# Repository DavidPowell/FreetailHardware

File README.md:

Hardware for Freetail module

Teensy 3.2 Symbol and Footprint adapted from work of Ricardo Band, under MIT License:
https://github.com/XenGi/teensy.pretty
https://github.com/XenGi/teensy_library

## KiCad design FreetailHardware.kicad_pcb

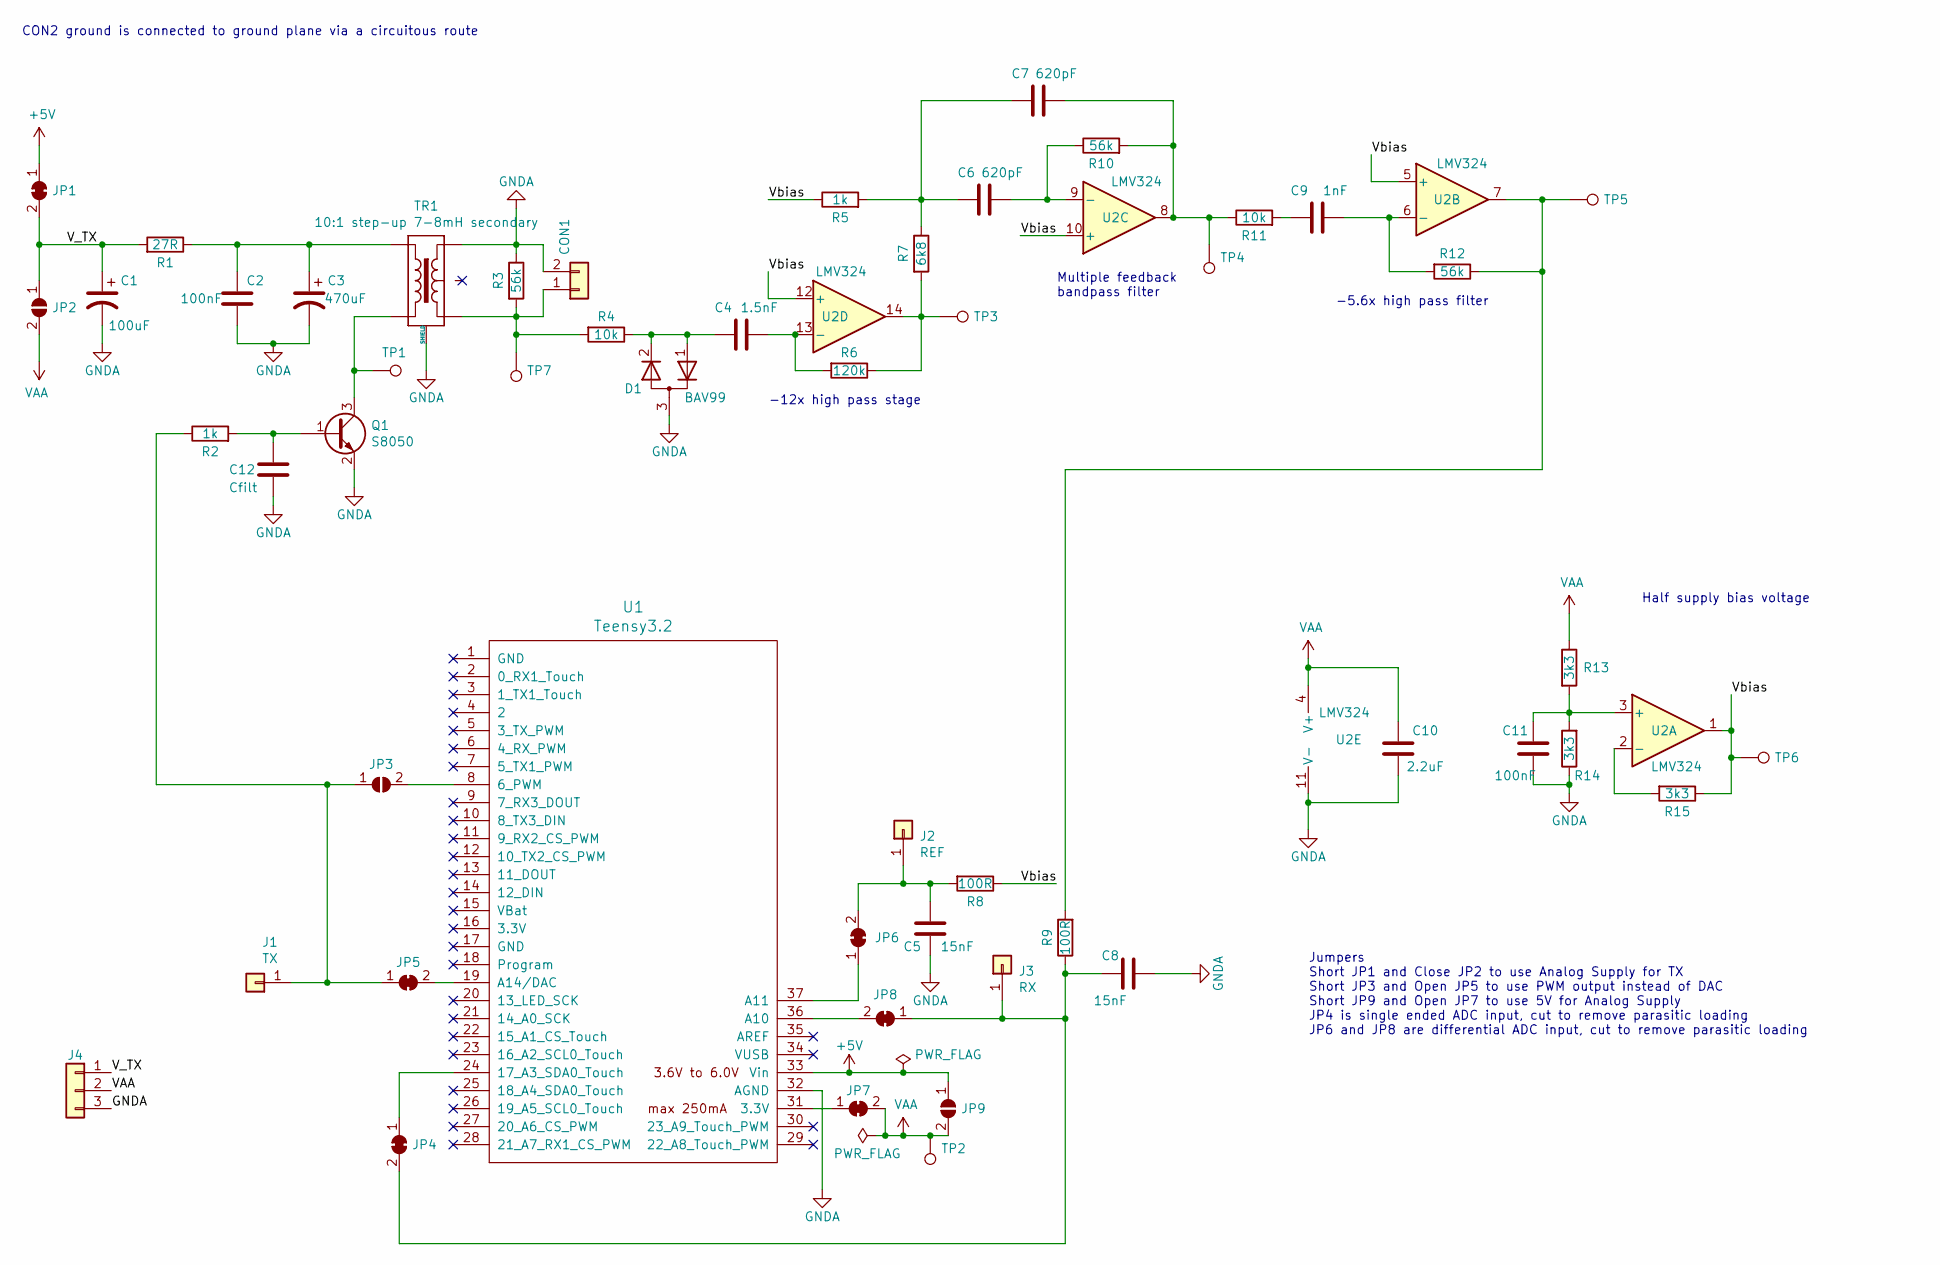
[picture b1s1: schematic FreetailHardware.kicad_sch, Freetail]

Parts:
C1: 100uF; CP_Radial_D5.0mm_P2.00mm; Digikey Part 732-8702-1-ND
C2, C11: 100nF; C_0603_1608Metric_Pad1.08x0.95mm_HandSolder; Digikey Part 1276-1006-1-ND
C3: 470uF; CP_Radial_D6.3mm_P2.50mm; Digikey Part 732-8708-1-ND
C4: 1.5nF; C_0603_1608Metric_Pad1.08x0.95mm_HandSolder; Digikey Part 1276-6666-1-ND
C5, C8: 15nF; C_0603_1608Metric_Pad1.08x0.95mm_HandSolder; Digikey Part 478-06033C153JAT2ACT-ND
C6, C7: 620pF; C_0603_1608Metric_Pad1.08x0.95mm_HandSolder; Digikey Part 1292-1540-1-ND
C9: 1nF; C_0603_1608Metric_Pad1.08x0.95mm_HandSolder; Digikey Part 478-1187-1-ND
C10: 2.2uF; C_0603_1608Metric_Pad1.08x0.95mm_HandSolder; Digikey Part 1276-1085-1-ND
C12: Cfilt; C_0603_1608Metric_Pad1.08x0.95mm_HandSolder
CON1: Transducer; PinHeader_1x02_P2.54mm_Vertical
D1: BAV99; SOT-323_SC-70_Handsoldering; Digikey Part 1727-6384-1-ND
J1: TX; PinHeader_1x01_P2.54mm_Vertical
J2: REF; PinHeader_1x01_P2.54mm_Vertical
J3: RX; PinHeader_1x01_P2.54mm_Vertical
J4: Conn_01x03; PinHeader_1x03_P2.54mm_Vertical
JP1, JP4, JP5, JP6, JP7, JP8: SolderJumper_2_Bridged; SolderJumper-2_P1.3mm_Bridged_RoundedPad1.0x1.5mm
JP2, JP3, JP9: SolderJumper_2_Open; SolderJumper-2_P1.3mm_Open_RoundedPad1.0x1.5mm
Q1: S8050; SOT-23_Handsoldering; Digikey Part 641-1790-1-ND
R1: 27R; R_0603_1608Metric_Pad0.98x0.95mm_HandSolder; Digikey Part RMCF0603FT27R0CT-ND
R2, R5: 1k; R_0603_1608Metric_Pad0.98x0.95mm_HandSolder; Digikey Part RMCF0603FT1K00CT-ND
R3, R10: 56k; R_0603_1608Metric_Pad0.98x0.95mm_HandSolder; Digikey Part RMCF0603FT56K0CT-ND
R4, R11: 10k; R_0603_1608Metric_Pad0.98x0.95mm_HandSolder; Digikey Part YAG2321CT-ND
R6: 120k; R_0603_1608Metric_Pad0.98x0.95mm_HandSolder; Digikey Part RMCF0603FT120KCT-ND
R7: 6k8; R_0603_1608Metric_Pad0.98x0.95mm_HandSolder; Digikey Part RMCF0603FT6K80CT-ND
R8, R9: 100R; R_0603_1608Metric_Pad0.98x0.95mm_HandSolder; Digikey Part RMCF0603FT100RCT-ND
R12: 56k; R_0603_1608Metric_Pad0.98x0.95mm_HandSolder; Digikey Part RMCF0603FT470KCT-ND
R13, R14, R15: 3k3; R_0603_1608Metric_Pad0.98x0.95mm_HandSolder; Digikey Part 311-3.30KHRCT-ND
TP1, TP2, TP3, TP4, TP5, TP6, TP7: TestPoint; TestPoint_THTPad_D1.5mm_Drill0.7mm
TR1: 10:1 step-up 7-8mH secondary; Ultrasonic transformer
U1: Teensy3.2; Teensy32
U2: LMV324; TSSOP-14_4.4x5mm_P0.65mm; Digikey Part LMV324TSG-13DICT-ND

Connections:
+5V: JP1.1 (A), JP9.1 (A), U1.33 (Vin)
/V_TX: C1.1, J4.1, JP1.2 (B), JP2.1 (A), R1.2
/Vbias: R5.1, R8.1, R15.1, TP6.1, U2.1, U2.5 (+), U2.10 (+), U2.12 (+)
GNDA: C1.2, C2.1, C3.2, C5.1, C8.2, C10.1, C11.1, C12.2, CON1.2, D1.3 (A), J4.3, Q1.2 (E), R3.1, R14.1, TR1.3, TR1.7 (SHIELD), TR1.8, U1.32 (AGND), U2.11 (V-)
unnamed: C2.2, C3.1, R1.1, TR1.4
unnamed: C4.1, R6.2, U2.13 (-)
unnamed: C4.2, D1.1 (K), D1.2 (K), R4.1
unnamed: C5.2, J2.1, JP6.2 (B), R8.2
unnamed: C6.1, R10.1, U2.9 (-)
unnamed: C6.2, C7.2, R5.2, R7.1
unnamed: C7.1, R10.2, R11.1, TP4.1, U2.8
unnamed: C8.1, J3.1, JP4.2 (B), JP8.1 (A), R9.1
unnamed: C9.1, R12.2, U2.6 (-)
unnamed: C9.2, R11.2
unnamed: C11.2, R13.2, R14.2, U2.3 (+)
unnamed: CON1.1, R3.2, R4.2, TP7.1, TR1.1
unnamed: J1.1, JP3.1 (A), JP5.1 (A), R2.1
unnamed: JP3.2 (B), U1.8 (6_PWM)
unnamed: JP4.1 (A), U1.24 (17_A3_SDA0_Touch)
unnamed: JP5.2 (B), U1.19 (A14/DAC)
unnamed: JP6.1 (A), U1.37 (A11)
unnamed: JP7.1 (A), U1.31 (3.3V)
unnamed: JP8.2 (B), U1.36 (A10)
unnamed: C12.1, Q1.1 (B), R2.2
unnamed: Q1.3 (C), TP1.1, TR1.6
unnamed: R6.1, R7.2, TP3.1, U2.14
unnamed: R9.2, R12.1, TP5.1, U2.7
unnamed: R15.2, U2.2 (-)
VAA: C10.2, J4.2, JP2.2 (B), JP7.2 (B), JP9.2 (B), R13.1, TP2.1, U2.4 (V+)

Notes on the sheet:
-12x high pass stage
Jumpers Short JP1 and Close JP2 to use Analog Supply for TX Short JP3 and Open JP5 to use PWM output instead of DAC Short JP9 and Open JP7 to use 5V for Analog Supply JP4 is single ended ADC input, cut to remove parasitic loading JP6 and JP8 are differential ADC input, cut to remove parasitic loadi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
Multiple feedback bandpass filter
-5.6x high pass filter
CON2 ground is connected to ground plane via a circuitous route
Half supply bias voltage

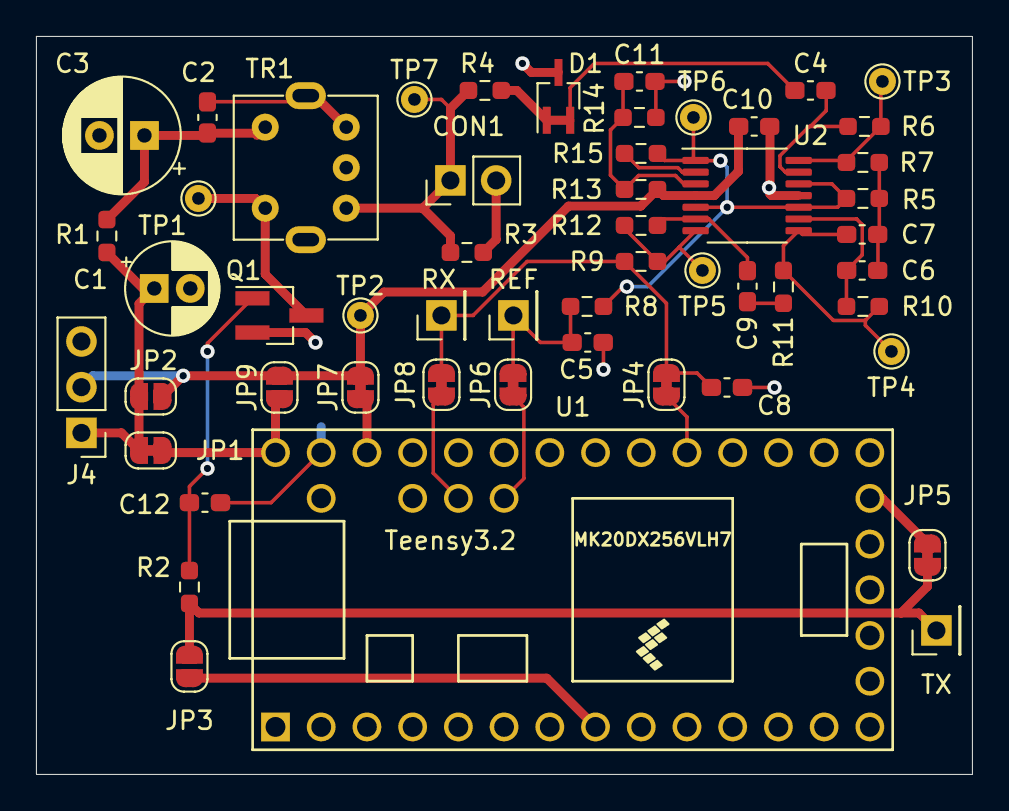
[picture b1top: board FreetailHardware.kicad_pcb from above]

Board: 2 copper layers, 52.0 x 41.0 mm, 54 parts (1 on the bottom side), 29 nets.

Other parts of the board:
Logo: Logo; freetail

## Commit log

2022-01-10 Version 1.0, as fabricated
2022-01-10 Updated to KiCad v6
2022-01-10 Update R12 to 56k to reduce final stage gain
2022-01-13 v1.1 Hardware sent for fabrication
2022-02-04 Version 1.2 sent for fabrication Fix unconnected Vbias Mark soldered pads for Teensy Add capacitor for TX filter
2022-02-10 Added BOM for 1.3 design
